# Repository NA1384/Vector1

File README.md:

# Vector 1
Vector 1 is a thrust-vectoring model rocket computer with all the hardware required to keep your TVC model rocket upright. 

If you have any question, comments or advice on how to use the flight computer don't hesitate to open an issue.

<div style="display:flex">

</div>

## Feature Set

- Main microcontroller is an Atmel ATSAMD21G18 with a 32-Bit ARM® Cortex® M0+ core running at 48 MHz with 256 KB of flash. 
- High performance sensor suite with the Bosch BMI088 6-axis IMU and the TE MS5611 high accuracy barometer.
- 3 servo outputs, two for thrust-vectoring gimbal and one for a mechanical chute ejection system or any other necessary servo actions.
- 4 pyrotechnic outputs for nichrome wire, black powder parachute ejection charges or igniting a secondary motor. Pyro channels 3 & 4 are PWM capable allowing for variable current outputs through software making them more suitable for nichrome wire outputs. Continuity detection on all channels.
- DC motor driver for roll control through a reaction wheel. 
- 32 Mb non-volatile flash storage for data recording during flight along with a microSD card port to retrieve flight data after the flight.
- RGB LED and buzzer for state indication. The LED is also setup to indicate serial communications to and from the microcontroller.
- Board is 40mm wide and 75mm tall and has 4 layers. All components except for servo outputs and terminals are SMD.

## Flight Software

Full flight software will be released soon for a complete electronics solution for TVC model rockets.

## Schematic & Board Preview

<div style="display:flex">

</div>

## Repository Contents

* **/Schematic & Board files** - Eagle design files (.brd, .sch) divided into folders based on silkscreen language and PDF of schematic
* **/Images** - Images of the built board and schematic

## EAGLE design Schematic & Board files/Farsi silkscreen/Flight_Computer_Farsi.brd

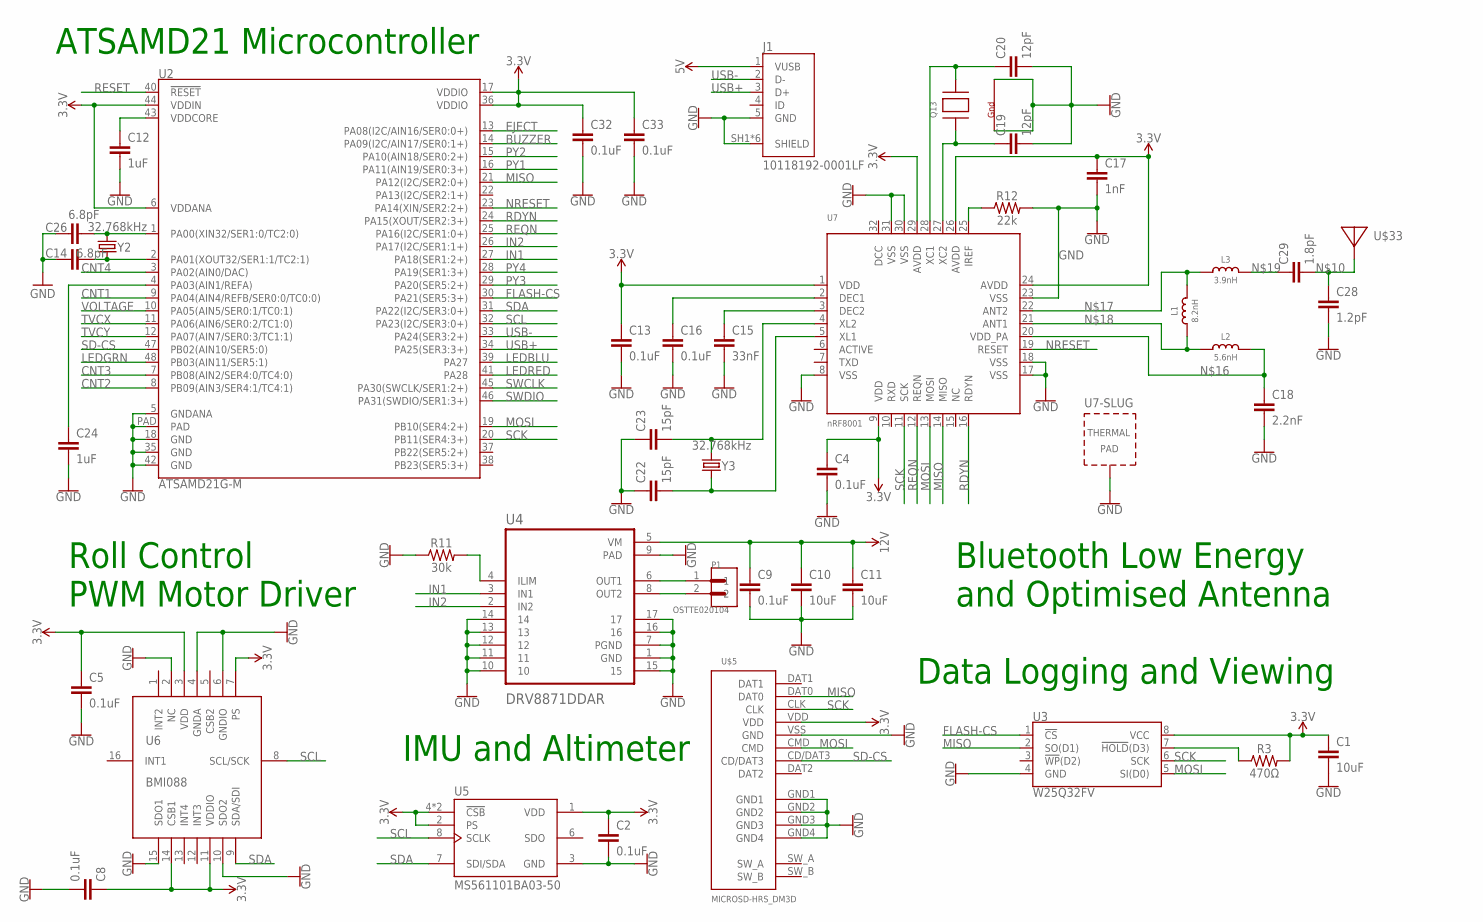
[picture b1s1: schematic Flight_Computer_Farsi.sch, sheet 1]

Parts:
C1, C10, C11: 10uF; 0603
C2, C4, C5, C8, C13, C16, C32, C33: 0.1uF; 0402
C9: 0.1uF; 0603
C12, C24: 1uF; 0603
C14, C26: 6.8pF; 0603
C15: 33nF; 0402
C17: 1nF; 0402
C18: 2.2nF; 0402
C19, C20: 12pF; 0402
C22, C23: 15pF; 0402
C28: 1.2pF; 0402
C29: 1.8pF; 0402
J1: 10118192-0001LF; AMPHENOL_10118192-0001LF
L1: 8.2nH; _0402
L2: 5.6nH; _0402
L3: 3.9nH; _0402
P1: OSTTE020104; OST_OSTTE020104
Q13: XTAL-4-3225; NX3225
R3: 470Ω; 0603
R11: 30k; 0603
R12: 22k; 0402
U2: ATSAMD21G-M; QFN-48
U3: W25Q32FV; SOIC-8
U4: DRV8871DDAR; VREG_LM5017MR/NOPB
U5: MS561101BA03-50; SON125P500X300X100-8N
U6: BMI088
U7: nRF8001; QFN32_5MM
U$5: MICROSD-HRS_DM3D; DM3D
U$33: ANTENNA_PCBNRF8001_1.6MM_REV; ANT_PCB_2.4GHZ_NRF8001_1.6MM_1OZ_REV
Y2, Y3: 32.768kHz; CRYSTAL-SMD-3.2X1.5MM

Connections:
3.3V: C1.1, C2.1, C4.1, C5.1, C8.1, C13.1, C17.1, C32.1, C33.1, R3.2, U2.6 (VDDANA), U2.17 (VDDIO), U2.36 (VDDIO), U2.44 (VDDIN), U3.8 (VCC), U5.1 (VDD), U5.2 (PS), U5.4 (!CSB), U5.5 (!CSB), U6.3 (VDD), U6.7 (PS), U6.11 (VDDIO), U6.14 (CSB1), U7.1 (VDD), U7.9 (VDD), U7.24 (AVDD), U7.26 (AVDD), U7.29 (AVDD), U$5.VDD; also elsewhere on the board
5V: J1.1 (VUSB); also elsewhere on the board
12V: C9.1, C10.1, C11.1, U4.5 (VM); also elsewhere on the board
BUZZER: U2.14 (PA09(I2C/AIN17/SER0:1+)); also elsewhere on the board
CNT1: U2.9 (PA04(AIN4/REFB/SER0:0/TC0:0)); also elsewhere on the board
CNT2: U2.8 (PB09(AIN3/SER4:1/TC4:1)); also elsewhere on the board
CNT3: U2.7 (PB08(AIN2/SER4:0/TC4:0)); also elsewhere on the board
CNT4: U2.3 (PA02(AIN0/DAC)); also elsewhere on the board
EJECT: U2.13 (PA08(I2C/AIN16/SER0:0+)); also elsewhere on the board
FLASH-CS: U2.30 (PA21(SER5:3+)), U3.1 (!CS!)
GND: C1.2, C2.2, C4.2, C5.2, C8.2, C9.2, C10.2, C11.2, C12.2, C13.2, C14.1, C15.2, C16.2, C17.2, C18.2, C19.2, C20.2, C22.1, C23.1, C24.2, C26.1, C28.2, C32.2, C33.2, J1.5 (GND), J1.SH1 (SHIELD), J1.SH2 (SHIELD), J1.SH3 (SHIELD), J1.SH4 (SHIELD), J1.SH5 (SHIELD), J1.SH6 (SHIELD), Q13.2 (G2), Q13.4 (G1), R11.1, R12.2, U2.5 (GNDANA), U2.18 (GND), U2.35 (GND), U2.42 (GND), U2.PAD, U3.4 (GND), U4.1 (GND), U4.7 (PGND), U4.9 (PAD), U4.10, U4.11, U4.12, U4.13, U4.14, U4.15, U4.16, U4.17, U5.3 (GND), U6.2 (NC), U6.4 (GNDA), U6.6 (GNDIO), U6.10 (SDO2), U6.15 (SDO1), U7.8 (VSS), U7.17 (VSS), U7.18 (VSS), U7.23 (VSS), U7.30 (VSS), U7.31 (VSS), U7.33 (TP), U$5.GND1, U$5.GND2, U$5.GND3, U$5.GND4, U$5.VSS (GND); also elsewhere on the board
IN1: U2.27 (PA18(SER1:2+)), U4.3 (IN1)
IN2: U2.26 (PA17(I2C/SER1:1+)), U4.2 (IN2)
LEDBLU: U2.39 (PA27); also elsewhere on the board
LEDGRN: U2.48 (PB03(AIN11/SER5:1)); also elsewhere on the board
LEDRED: U2.41 (PA28); also elsewhere on the board
MISO: U2.21 (PA12(I2C/SER2:0+)), U3.2 (SO(D1)), U7.14 (MISO), U$5.DAT0
MOSI: U2.19 (PB10(SER4:2+)), U3.5 (SI(D0)), U7.13 (MOSI), U$5.CMD
unnamed: R3.1, U3.7 (!HOLD!(D3))
unnamed: C12.1, U2.43 (VDDCORE)
unnamed: R11.2, U4.4 (ILIM)
unnamed: P1.1, U4.6 (OUT1)
unnamed: C28.1, C29.2, U$33.FEED
unnamed: P1.2, U4.8 (OUT2)
unnamed: C15.1, U7.3 (DEC2)
unnamed: C16.1, U7.2 (DEC1)
unnamed: R12.1, U7.25 (IREF)
unnamed: C18.1, L2.2, U7.20 (VDD_PA)
unnamed: L1.2, L3.1, U7.22 (ANT2)
unnamed: L1.1, L2.1, U7.21 (ANT1)
unnamed: C29.1, L3.2
unnamed: C20.1, Q13.3 (X2), U7.28 (XC1)
unnamed: C19.1, Q13.1 (X1), U7.27 (XC2)
unnamed: C23.2, U7.4 (XL2), Y3.P$2 (2)
unnamed: C22.2, U7.5 (XL1), Y3.P$1 (1)
unnamed: C24.1, U2.4 (PA03(AIN1/REFA))
unnamed: C26.2, U2.1 (PA00(XIN32/SER1:0/TC2:0)), Y2.P$2 (2)
unnamed: C14.2, U2.2 (PA01(XOUT32/SER1:1/TC2:1)), Y2.P$1 (1)
NRESET: U2.23 (PA14(XIN/SER2:2+)), U7.19 (RESET)
PY1: U2.16 (PA11(AIN19/SER0:3+)); also elsewhere on the board
PY2: U2.15 (PA10(AIN18/SER0:2+)); also elsewhere on the board
PY3: U2.29 (PA20(SER5:2+)); also elsewhere on the board
PY4: U2.28 (PA19(SER1:3+)); also elsewhere on the board
RDYN: U2.24 (PA15(XOUT/SER2:3+)), U7.16 (RDYN)
REQN: U2.25 (PA16(I2C/SER1:0+)), U7.12 (REQN)
RESET: U2.40 (!RESET!); also elsewhere on the board
SCK: U2.20 (PB11(SER4:3+)), U3.6 (SCK), U7.11 (SCK), U$5.CLK
SCL: U2.32 (PA23(I2C/SER3:0+)), U5.8 (SCLK), U6.8 (SCL/SCK); also elsewhere on the board
SD-CS: U2.47 (PB02(AIN10/SER5:0)), U$5.CD/DAT3
SDA: U2.31 (PA22(I2C/SER3:0+)), U5.7 (SDI/SDA), U6.9 (SDA/SDI); also elsewhere on the board
SWCLK: U2.45 (PA30(SWCLK/SER1:2+)); also elsewhere on the board
SWDIO: U2.46 (PA31(SWDIO/SER1:3+)); also elsewhere on the board
TVCX: U2.11 (PA06(AIN6/SER0:2/TC1:0)); also elsewhere on the board
TVCY: U2.12 (PA07(AIN7/SER0:3/TC1:1)); also elsewhere on the board
USB+: J1.3 (D+), U2.34 (PA25(SER3:3+)); also elsewhere on the board
USB-: J1.2 (D-), U2.33 (PA24(SER3:2+)); also elsewhere on the board
VOLTAGE: U2.10 (PA05(AIN5/SER0:1/TC0:1)); also elsewhere on the board

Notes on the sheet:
Data Logging and Viewing
ATSAMD21 Microcontroller
IMU and Altimeter
Roll Control PWM Motor Driver
Bluetooth Low Energy and Optimised Antenna

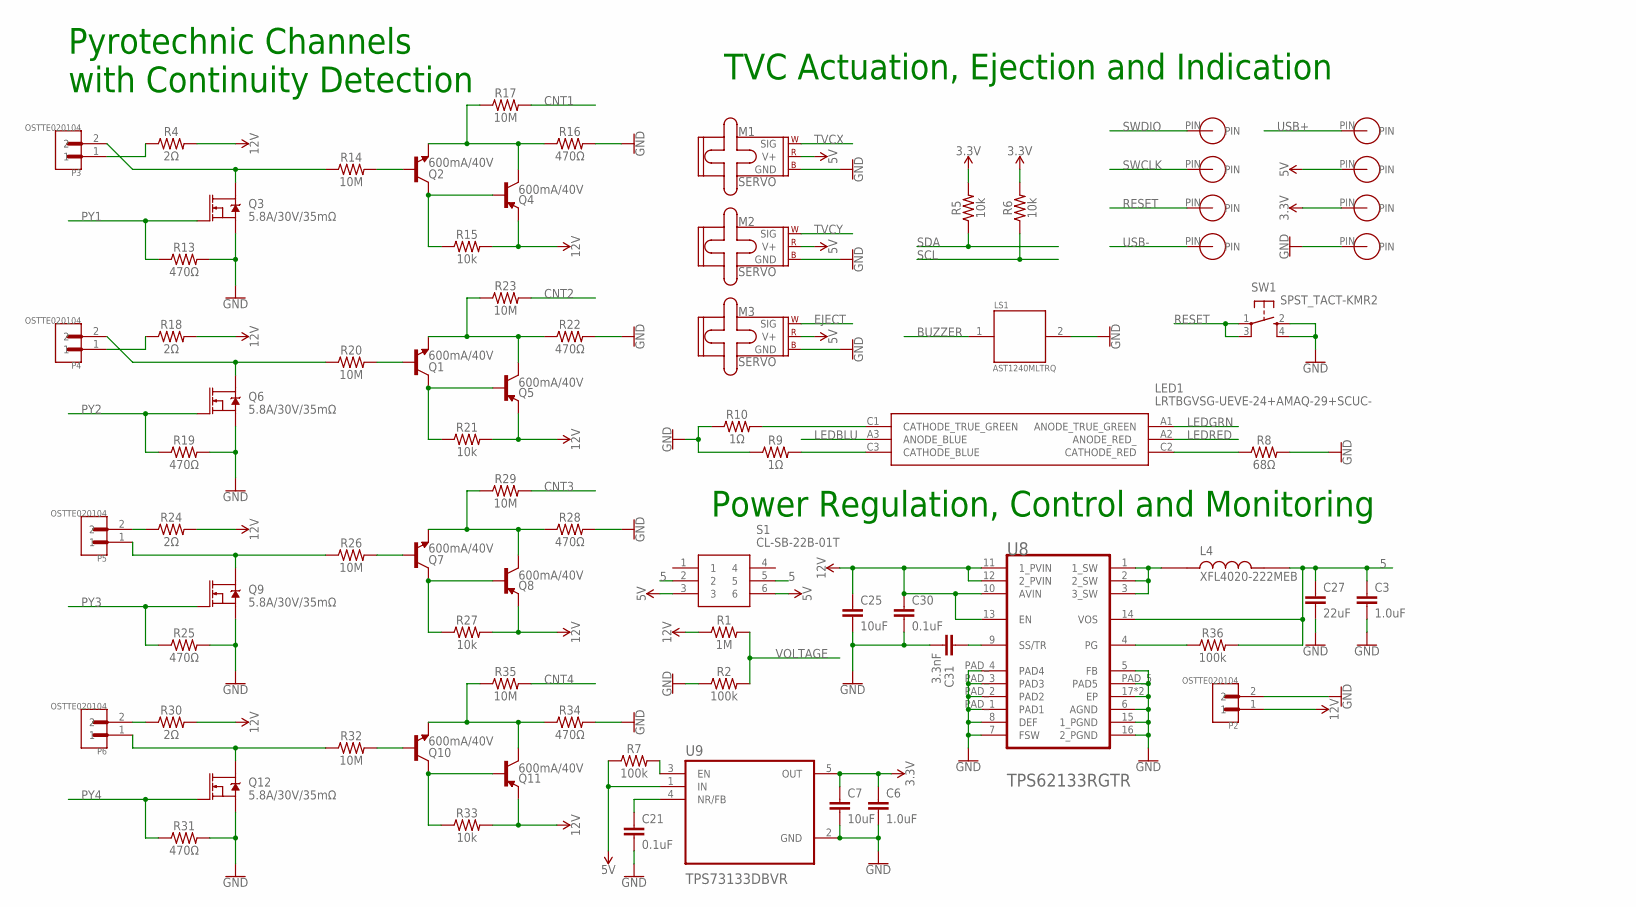
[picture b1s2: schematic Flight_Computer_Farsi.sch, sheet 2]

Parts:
C3, C6: 1.0uF; 0603
C7: 10uF; 0603
C21, C30: 0.1uF; 0603
C25: 10uF; 1210
C27: 22uF; 0805
C31: 3.3nF; 0603
L4: XFL4020-222MEB; IND_XFL4020-222MEB
LED1: LRTBGVSG-UEVE-24+AMAQ-29+SCUC-; LRTBGVSGUEVE24AMAQ29SCUCHR
LS1: AST1240MLTRQ; SPKR_AST1240MLTRQ
M1, M2, M3: SERVO; 1X03
P2, P3, P4, P5, P6: OSTTE020104; OST_OSTTE020104
Q1, Q2, Q4, Q5, Q7, Q8, Q10, Q11: 600mA/40V; SOT23-3
Q3, Q6, Q9, Q12: 5.8A/30V/35mΩ; SOT23-3
R1: 1M; 0603
R2, R7, R36: 100k; 0603
R4, R18, R24, R30: 2Ω; 0603
R5, R6: 10k; 0402
R8: 68Ω; 0402
R9, R10: 1Ω; 0402
R13, R16, R19, R22, R25, R28, R31, R34: 470Ω; 0603
R14, R17, R20, R23, R26, R29, R32, R35: 10M; 0603
R15, R21, R27, R33: 10k; 0603
S1: CL-SB-22B-01T; CLSB22B01T
SW1: SPST_TACT-KMR2; KMR2
U8: TEXAS_INSTRUMENTS_TPS62133RGTRTEXAS_INSTRUMENTS_T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; TEXAS_INSTRUMENTS_TPS62133RGTR_0
U9: TPS73133DBVR; SOT95P280X145-5N
U$8, U$9, U$10, U$11, U$12, U$13, U$14, U$15: CONTACT

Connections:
3.3V: C6.1, C7.1, R5.2, R6.2, U9.5 (OUT), U$14.PIN; also elsewhere on the board
5: C3.1, C27.1, L4.2, R36.2, S1.2, S1.5, U8.14 (VOS)
5V: M1.2 (V+), M2.2 (V+), M3.2 (V+), R7.1, S1.3, S1.6, U9.1 (IN), U$13.PIN; also elsewhere on the board
12V: C25.1, C30.1, P2.1, Q4.2 (E), Q5.2 (E), Q8.2 (E), Q11.2 (E), R1.1, R4.2, R15.2, R18.2, R21.2, R24.2, R27.2, R30.2, R33.2, U8.10 (AVIN), U8.11 (1_PVIN), U8.12 (2_PVIN), U8.13 (EN); also elsewhere on the board
BUZZER: LS1.1; also elsewhere on the board
CNT1: R17.2; also elsewhere on the board
CNT2: R23.2; also elsewhere on the board
CNT3: R29.2; also elsewhere on the board
CNT4: R35.2; also elsewhere on the board
EJECT: M3.1 (SIG); also elsewhere on the board
GND: C3.2, C6.2, C7.2, C21.2, C25.2, C27.2, C30.2, C31.2, LS1.2, M1.3 (GND), M2.3 (GND), M3.3 (GND), P2.2, Q3.2 (S), Q6.2 (S), Q9.2 (S), Q12.2 (S), R2.1, R8.2, R9.1, R10.1, R13.2, R16.2, R19.2, R22.2, R25.2, R28.2, R31.2, R34.2, SW1.2 (S), SW1.4 (S1), U8.5 (FB), U8.6 (AGND), U8.7 (FSW), U8.8 (DEF), U8.15 (1_PGND), U8.16 (2_PGND), U8.17 (EP), U8.17-2 (EP), U8.PAD_1 (PAD1), U8.PAD_2 (PAD2), U8.PAD_3 (PAD3), U8.PAD_4 (PAD4), U8.PAD_5 (PAD5), U9.2 (GND), U$12.PIN; also elsewhere on the board
LEDBLU: LED1.A3 (ANODE_BLUE); also elsewhere on the board
LEDGRN: LED1.A1 (ANODE_TRUE_GREEN); also elsewhere on the board
LEDRED: LED1.A2 (ANODE_RED_); also elsewhere on the board
unnamed: R7.2, U9.3 (EN)
unnamed: C21.1, U9.4 (NR/FB)
unnamed: LED1.C1 (CATHODE_TRUE_GREEN), R10.2
unnamed: LED1.C3 (CATHODE_BLUE), R9.2
unnamed: LED1.C2 (CATHODE_RED), R8.1
unnamed: P4.1, R18.1
unnamed: P3.1, R4.1
unnamed: P3.2, Q3.3 (D), R14.1
unnamed: Q2.1 (B), R14.2
unnamed: Q2.3 (C), Q4.1 (B), R15.1
unnamed: Q2.2 (E), Q4.3 (C), R16.1, R17.1
unnamed: L4.1, U8.1 (1_SW), U8.2 (2_SW), U8.3 (3_SW)
unnamed: R36.1, U8.4 (PG)
unnamed: C31.1, U8.9 (SS/TR)
unnamed: P4.2, Q6.3 (D), R20.1
unnamed: Q1.1 (B), R20.2
unnamed: Q1.3 (C), Q5.1 (B), R21.1
unnamed: Q1.2 (E), Q5.3 (C), R22.1, R23.1
unnamed: P5.1, Q9.3 (D), R26.1
unnamed: Q7.1 (B), R26.2
unnamed: Q7.3 (C), Q8.1 (B), R27.1
unnamed: Q7.2 (E), Q8.3 (C), R28.1, R29.1
unnamed: P5.2, R24.1
unnamed: P6.1, Q12.3 (D), R32.1
unnamed: Q10.1 (B), R32.2
unnamed: Q10.3 (C), Q11.1 (B), R33.1
unnamed: Q10.2 (E), Q11.3 (C), R34.1, R35.1
unnamed: P6.2, R30.1
PY1: Q3.1 (G), R13.1; also elsewhere on the board
PY2: Q6.1 (G), R19.1; also elsewhere on the board
PY3: Q9.1 (G), R25.1; also elsewhere on the board
PY4: Q12.1 (G), R31.1; also elsewhere on the board
RESET: SW1.1, SW1.3 (P1), U$10.PIN; also elsewhere on the board
SCL: R6.1; also elsewhere on the board
SDA: R5.1; also elsewhere on the board
SWCLK: U$9.PIN; also elsewhere on the board
SWDIO: U$8.PIN; also elsewhere on the board
TVCX: M1.1 (SIG); also elsewhere on the board
TVCY: M2.1 (SIG); also elsewhere on the board
USB+: U$15.PIN; also elsewhere on the board
USB-: U$11.PIN; also elsewhere on the board
VOLTAGE: R1.2, R2.2; also elsewhere on the board

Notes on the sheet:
Pyrotechnic Channels with Continuity Detection
Power Regulation, Control and Monitoring
TVC Actuation, Ejection and Indication

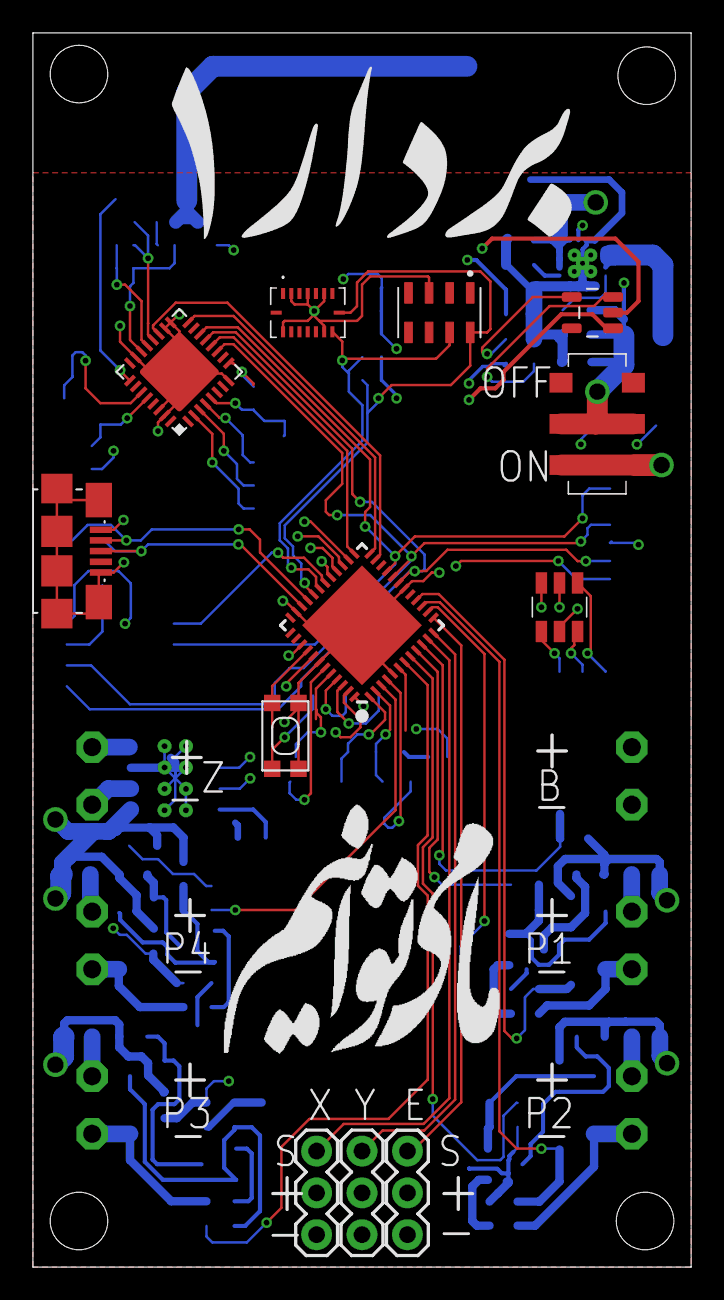
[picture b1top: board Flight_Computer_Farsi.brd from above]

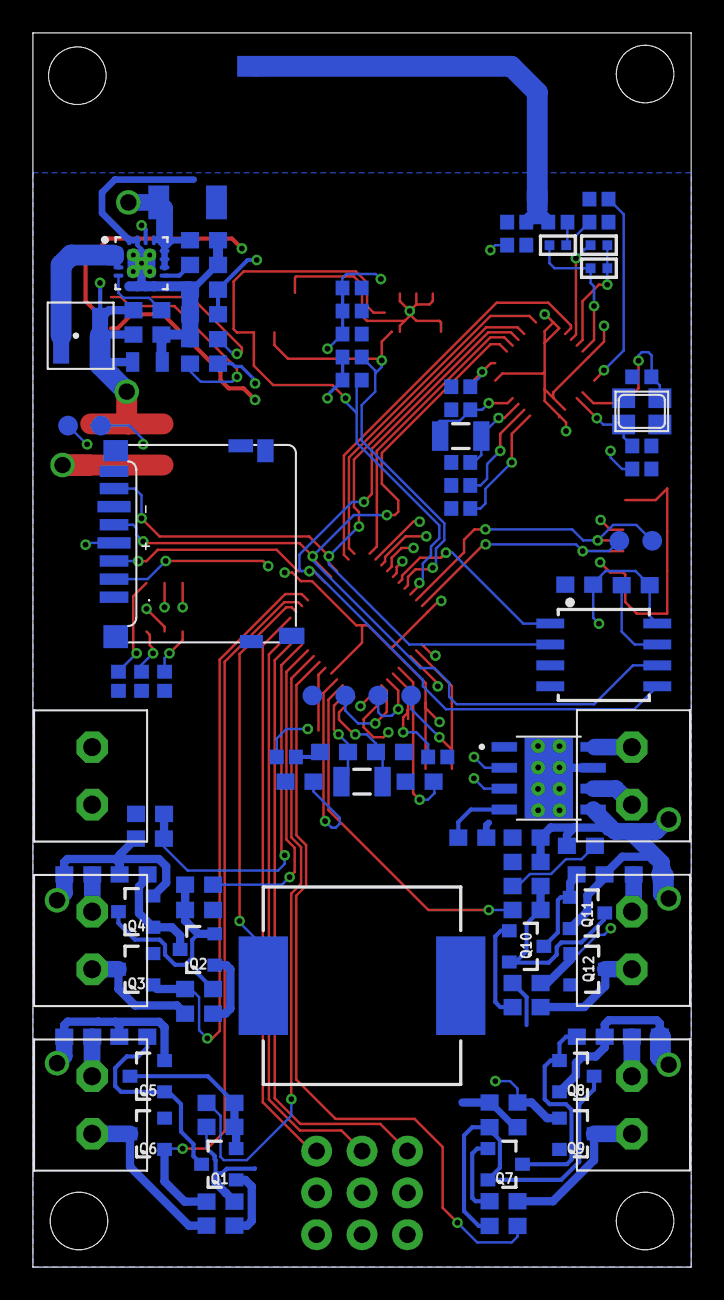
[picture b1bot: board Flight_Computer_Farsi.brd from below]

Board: 4 copper layers, 40.0 x 75.0 mm, 120 parts (108 on the bottom side), 86 nets.

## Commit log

2022-04-20 Eagle Schematic and Board files
    These are the eagle schematic and board files for the flight computer. There are two board files, one with the original Farsi (Persian) silkscreen and another in English with the name in English and 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
2022-04-20 Placed Eagle files in folder
2022-04-20 Images of Board
2022-04-21 Added more images
2022-04-21 PDF and organization
2022-04-21 Wrong size correction
2022-04-25 Google Verification Upload
    This will help the repo get discovered by more people and be useful to them.

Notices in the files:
parts and their libraries:
SparkFun-Capacitors: Licensing: Creative Commons ShareAlike 4.0 International - https://creativecommons.org/licenses/by-sa/4.0
microbuilder: This work is placed in the public domain, and may be freely used for commercial and non-commercial work with the following conditions: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
